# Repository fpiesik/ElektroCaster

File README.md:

What is the ElektroCaster?

The highest premise of the ElectroCaster is that it's a real guitar which can be used just like that. This project is about to extend the possibilities of expression of a guitar without taking anything away from it. By guitar I don't mean a specific instrument that's hacked somehow, but the idea of a guitar that's to be extended. The ElektroCaster is built from scratch out of aluminum, 3d printed PLA and wood. All the design files are made with open tools such as OpenScad and Kicad. The design is made with the option of parametric changes in mind, like changing the string count, for example.

Here is a list with the most important "guitar-extensions" I've implemented on the hardware side so far are:

    led lit fretboard with 150 individually controllable rbg-leds
    hexaphonic pickip along with a Teensy 4 based 6 channel dsp-unit
    actuator called Kickup that consists of 6 solenoid hitting the strings
    actuator called MultEbow that works like a polyphonic e-Bow (endless sustain)
    fretboard is "touch sensitive" in a way that it recognises which string was pressed at what position
    10 faders, 7 potis, 8 rotary encoder(&switches), 5 buttons, 7 toggle switches, 3 rotary switches (12steps), an analog joystick
    128*64 oled display

## Documentation quick reference

This repository contains three cooperating firmware targets. The tables below summarize the currently documented board roles, serial links, and hardware/protocol references without changing firmware behavior.

### Board roles

| Board firmware | Target noted in docs | Main role | Documentation |
| --- | --- | --- | --- |
| `software/firmwareHid` | Teensy 3.5 | Body controls, encoder/analog/digital input scanning, and local OLED rendering. | `docs/architecture.md`, `docs/protocols.md`, `docs/pinout.md` |
| `software/firmwareCtl` | Teensy 4.1 | Main controller for system state, LED fretboard, fretboard sensing, Kickup, MulEBow control, sequencer/MIDI/SD coordination, and board-to-board routing. | `docs/architecture.md`, `docs/protocols.md`, `docs/realtime.md` |
| `software/firmwareAudio` | Teensy 4.1 | Hexaphonic audio processing, pitch/amplitude analysis, per-string DSP, and actuator audio/control outputs. | `docs/architecture.md`, `docs/protocols.md`, `docs/realtime.md` |

### Serial protocol map

| Link | Baud | Purpose | Details |
| --- | ---: | --- | --- |
| HID <-> CTL | 115200 | Body-control events from HID to CTL and AsciiMassage display commands from CTL to HID. | `docs/protocols.md` |
| CTL <-> Audio | 250000 | Raw byte audio-control commands from CTL to Audio and pitch/amplitude status from Audio to CTL. | `docs/protocols.md` |

### Hardware and timing notes

| Topic | Documentation file | Notes |
| --- | --- | --- |
| Pin assignments | `docs/pinout.md` | Documents firmware-inferred pins only; hardware connector names remain open unless present in source. |
| Realtime intervals | `docs/realtime.md` | Documents LED, fretboard debounce, Kickup, display, clock, HID, and audio intervals. |
| Testing guidance | `docs/testing.md` | Lists safe checks and hardware validation areas. |

### User manual

The English, code-derived user manual is available at [`docs/user-manual.md`](docs/user-manual.md). It distinguishes implemented behavior from hardware details that cannot be confirmed from the repository.

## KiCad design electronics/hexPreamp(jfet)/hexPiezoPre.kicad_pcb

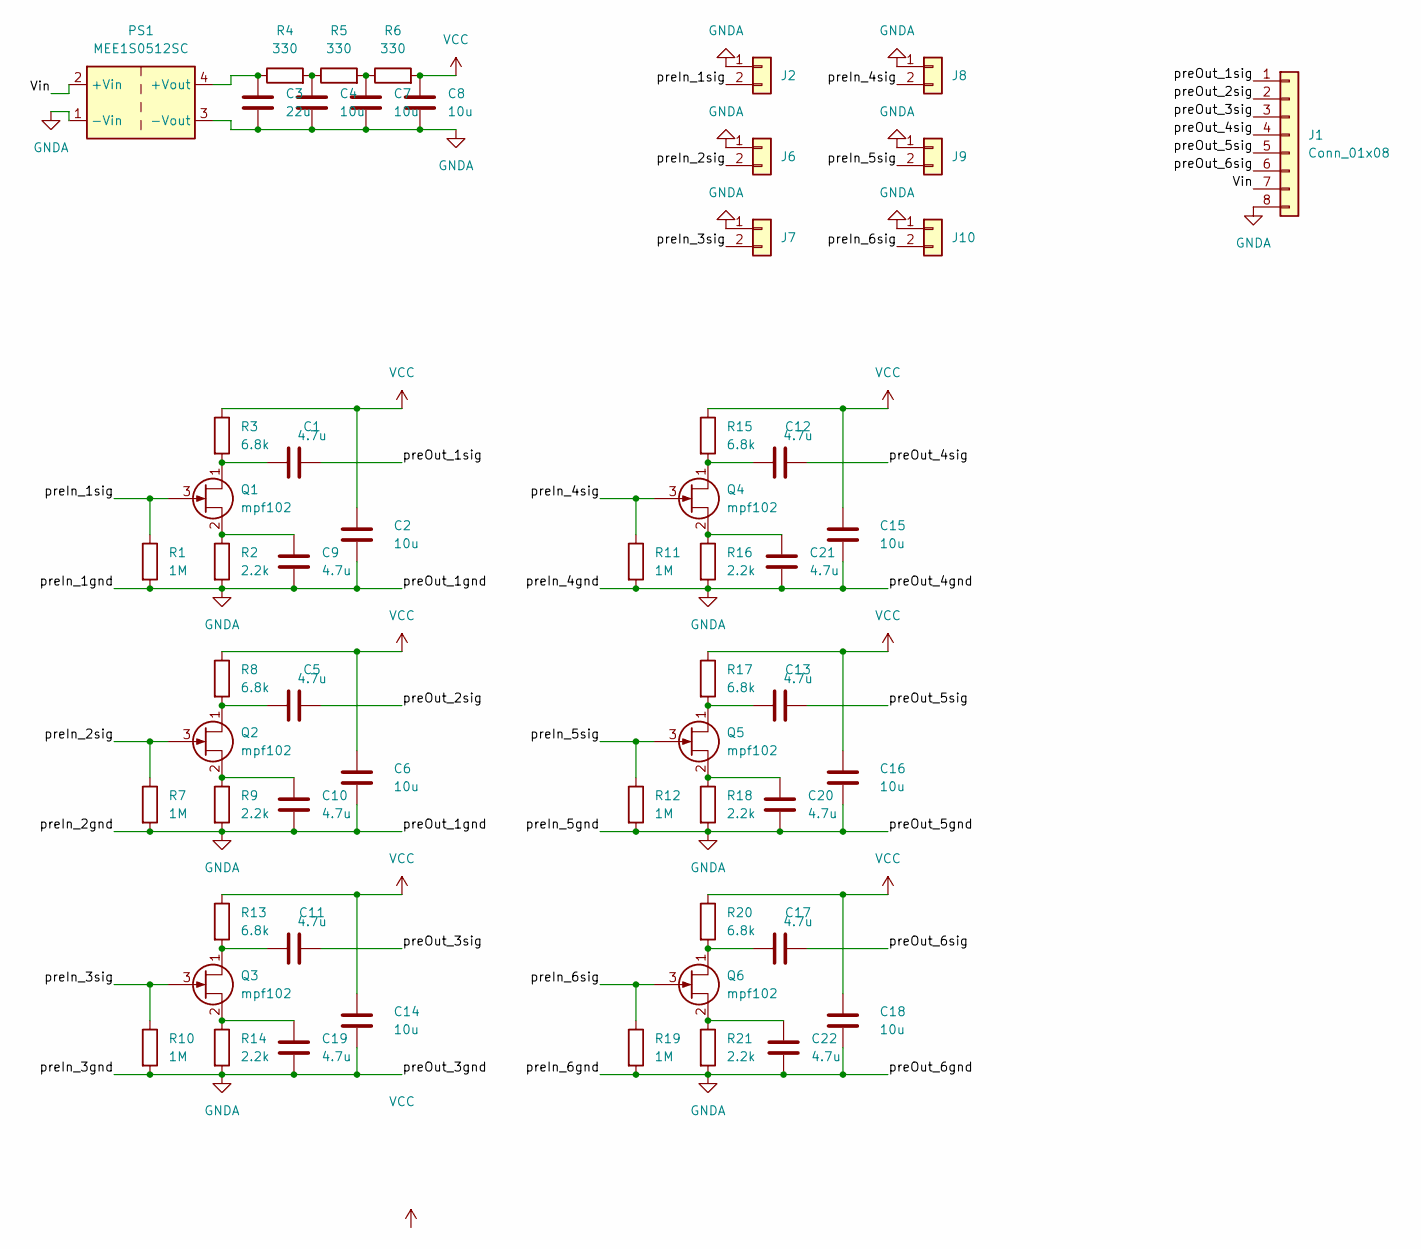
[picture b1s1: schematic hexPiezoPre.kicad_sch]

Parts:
C1, C5, C9, C10, C11, C12, C13, C17, C19, C20, C21, C22: 4.7u; C_0805_2012Metric_Pad1.18x1.45mm_HandSolder
C2, C4, C6, C7, C8, C14, C15, C16, C18: 10u; C_0805_2012Metric_Pad1.18x1.45mm_HandSolder
C3: 22u; C_0805_2012Metric_Pad1.18x1.45mm_HandSolder
J1: Conn_01x08; PinHeader_1x08_P2.54mm_Vertical
J2, J6, J7, J8, J9, J10: Conn_01x02; PinHeader_1x02_P2.54mm_Vertical
PS1: MEE1S0512SC; Converter_DCDC_Murata_MEE1SxxxxSC_THT
Q1, Q2, Q3, Q4, Q5, Q6: mpf102; TO-92
R1, R7, R10, R11, R12, R19: 1M; R_0805_2012Metric_Pad1.20x1.40mm_HandSolder
R2, R9, R14, R16, R18, R21: 2.2k; R_0805_2012Metric_Pad1.20x1.40mm_HandSolder
R3, R8, R13, R15, R17, R20: 6.8k; R_0805_2012Metric_Pad1.20x1.40mm_HandSolder
R4, R5, R6: 330; R_0805_2012Metric_Pad1.20x1.40mm_HandSolder

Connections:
/Vin: J1.7, PS1.2 (+Vin)
/preIn_1sig: J2.2, Q1.3 (G), R1.1
/preIn_2sig: J6.2, Q2.3 (G), R7.1
/preIn_3sig: J7.2, Q3.3 (G), R10.1
/preIn_4sig: J8.2, Q4.3 (G), R11.1
/preIn_5sig: J9.2, Q5.3 (G), R12.1
/preIn_6sig: J10.2, Q6.3 (G), R19.1
/preOut_1sig: C1.2, J1.1
/preOut_2sig: C5.2, J1.2
/preOut_3sig: C11.2, J1.3
/preOut_4sig: C12.2, J1.4
/preOut_5sig: C13.2, J1.5
/preOut_6sig: C17.2, J1.6
GNDA: C2.2, C3.2, C4.2, C6.2, C7.2, C8.2, C9.2, C10.2, C14.2, C15.2, C16.2, C18.2, C19.2, C20.2, C21.2, C22.2, J1.8, J2.1, J6.1, J7.1, J8.1, J9.1, J10.1, PS1.1 (-Vin), PS1.3 (-Vout), R1.2, R2.2, R7.2, R9.2, R10.2, R11.2, R12.2, R14.2, R16.2, R18.2, R19.2, R21.2
unnamed: C1.1, Q1.1 (D), R3.2
unnamed: C3.1, PS1.4 (+Vout), R4.1
unnamed: C4.1, R4.2, R5.1
unnamed: C5.1, Q2.1 (D), R8.2
unnamed: C7.1, R5.2, R6.1
unnamed: C9.1, Q1.2 (S), R2.1
unnamed: C10.1, Q2.2 (S), R9.1
unnamed: C11.1, Q3.1 (D), R13.2
unnamed: C12.1, Q4.1 (D), R15.2
unnamed: C13.1, Q5.1 (D), R17.2
unnamed: C17.1, Q6.1 (D), R20.2
unnamed: C19.1, Q3.2 (S), R14.1
unnamed: C20.1, Q5.2 (S), R18.1
unnamed: C21.1, Q4.2 (S), R16.1
unnamed: C22.1, Q6.2 (S), R21.1
VCC: C2.1, C6.1, C8.1, C14.1, C15.1, C16.1, C18.1, R3.1, R6.2, R8.1, R13.1, R15.1, R17.1, R20.1

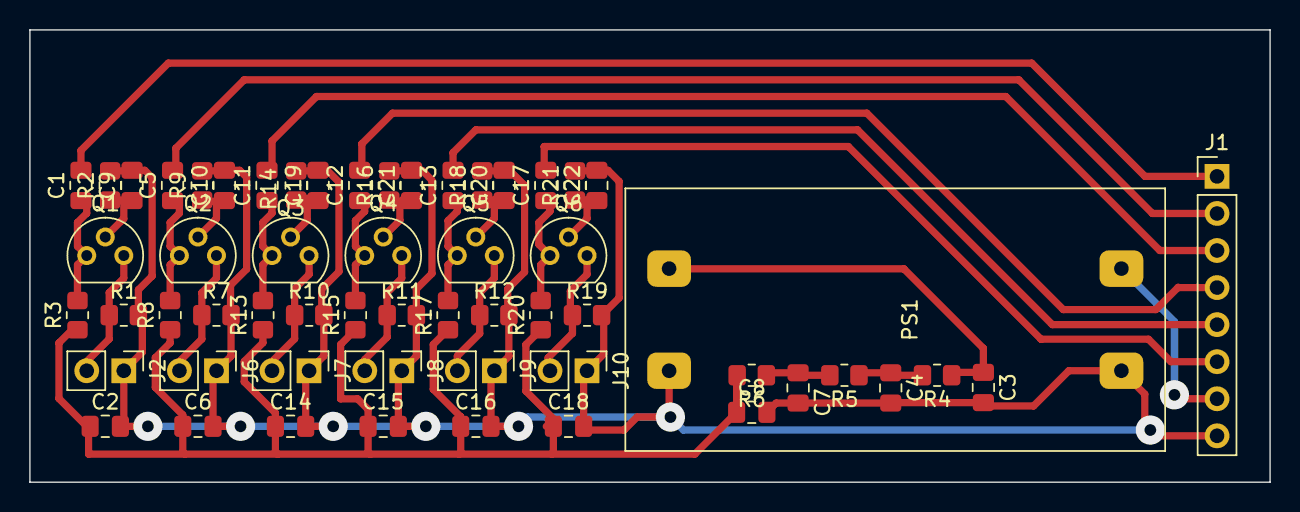
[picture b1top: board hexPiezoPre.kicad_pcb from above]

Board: 2 copper layers, 85.0 x 31.0 mm, 57 parts (0 on the bottom side), 30 nets.

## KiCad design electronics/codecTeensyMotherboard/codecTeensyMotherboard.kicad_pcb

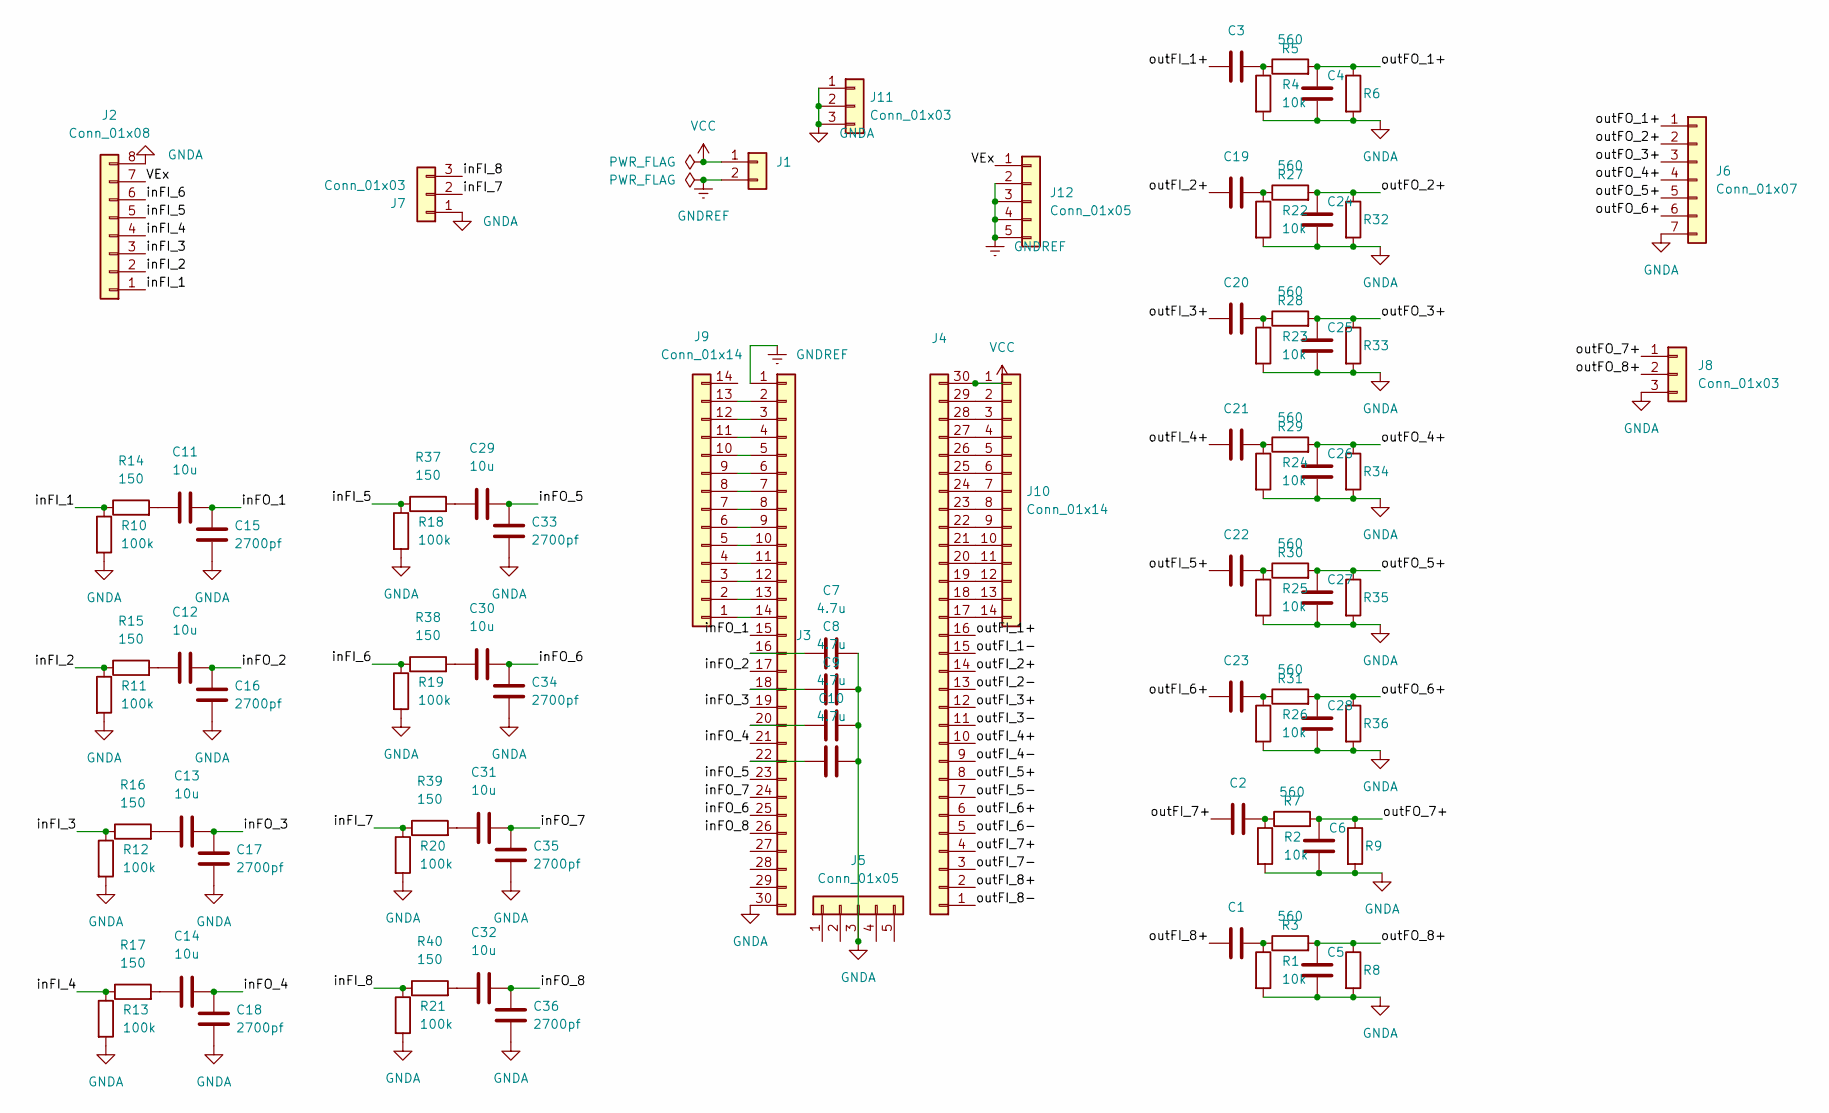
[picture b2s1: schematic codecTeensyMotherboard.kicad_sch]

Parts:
C1, C2, C3, C19, C20, C21, C22, C23: 3.3u; C_0805_2012Metric_Pad1.18x1.45mm_HandSolder
C4, C5, C6, C24, C25, C26, C27, C28: CAP; C_0805_2012Metric_Pad1.18x1.45mm_HandSolder
C7, C8, C9, C10: 4.7u; C_0805_2012Metric_Pad1.18x1.45mm_HandSolder
C11, C12, C13, C14, C29, C30, C31, C32: 10u; C_0805_2012Metric_Pad1.18x1.45mm_HandSolder
C15, C16, C17, C18, C33, C34, C35, C36: 2700pf; C_0805_2012Metric_Pad1.18x1.45mm_HandSolder
J1: Conn_01x02; PinHeader_1x02_P2.54mm_Vertical
J2: Conn_01x08; PinHeader_1x08_P2.54mm_Vertical
J3, J4: Conn_01x30; PinHeader_1x30_P2.54mm_Vertical
J5, J12: Conn_01x05; PinHeader_1x05_P2.54mm_Vertical
J6: Conn_01x07; PinHeader_1x07_P2.54mm_Vertical
J7, J8, J11: Conn_01x03; PinHeader_1x03_P2.54mm_Vertical
J9, J10: Conn_01x14; PinHeader_1x14_P2.54mm_Vertical
R1, R2, R4, R22, R23, R24, R25, R26: 10k; R_0805_2012Metric_Pad1.20x1.40mm_HandSolder
R3, R5, R7, R27, R28, R29, R30, R31: 560; R_0805_2012Metric_Pad1.20x1.40mm_HandSolder
R6, R8, R9, R32, R33, R34, R35, R36: R; R_0805_2012Metric_Pad1.20x1.40mm_HandSolder
R10, R11, R12, R13, R18, R19, R20, R21: 100k; R_0805_2012Metric_Pad1.20x1.40mm_HandSolder
R14, R15, R16, R17, R37, R38, R39, R40: 150; R_0805_2012Metric_Pad1.20x1.40mm_HandSolder

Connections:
/VEx: J2.7, J12.1
/inFI_1: J2.1, R10.1, R14.1
/inFI_2: J2.2, R11.1, R15.1
/inFI_3: J2.3, R12.1, R16.1
/inFI_4: J2.4, R13.1, R17.1
/inFI_5: J2.5, R18.1, R37.1
/inFI_6: J2.6, R19.1, R38.1
/inFI_7: J7.2, R20.1, R39.1
/inFI_8: J7.3, R21.1, R40.1
/inFO_1: C11.2, C15.2, J3.15
/inFO_2: C12.2, C16.2, J3.17
/inFO_3: C13.2, C17.2, J3.19
/inFO_4: C14.2, C18.2, J3.21
/inFO_5: C29.2, C33.2, J3.23
/inFO_6: C30.2, C34.2, J3.25
/inFO_7: C31.2, C35.2, J3.24
/inFO_8: C32.2, C36.2, J3.26
/outFI_1+: C3.1, J4.16
/outFI_1-: J4.15
/outFI_2+: C19.1, J4.14
/outFI_2-: J4.13
/outFI_3+: C20.1, J4.12
/outFI_3-: J4.11
/outFI_4+: C21.1, J4.10
/outFI_4-: J4.9
/outFI_5+: C22.1, J4.8
/outFI_5-: J4.7
/outFI_6+: C23.1, J4.6
/outFI_6-: J4.5
/outFI_7+: C2.1, J4.4
/outFI_7-: J4.3
/outFI_8+: C1.1, J4.2
/outFI_8-: J4.1
/outFO_1+: C4.1, J6.1, R5.2, R6.1
/outFO_2+: C24.1, J6.2, R27.2, R32.1
/outFO_3+: C25.1, J6.3, R28.2, R33.1
/outFO_4+: C26.1, J6.4, R29.2, R34.1
/outFO_5+: C27.1, J6.5, R30.2, R35.1
/outFO_6+: C28.1, J6.6, R31.2, R36.1
/outFO_7+: C6.1, J8.1, R7.2, R9.1
/outFO_8+: C5.1, J8.2, R3.2, R8.1
GNDA: C4.2, C5.2, C6.2, C7.2, C8.2, C9.2, C10.2, C15.1, C16.1, C17.1, C18.1, C24.2, C25.2, C26.2, C27.2, C28.2, C33.1, C34.1, C35.1, C36.1, J2.8, J3.30, J5.3, J6.7, J7.1, J8.3, J11.1, J11.2, J11.3, R1.2, R2.2, R4.2, R6.2, R8.2, R9.2, R10.2, R11.2, R12.2, R13.2, R18.2, R19.2, R20.2, R21.2, R22.2, R23.2, R24.2, R25.2, R26.2, R32.2, R33.2, R34.2, R35.2, R36.2
GNDREF: J1.2, J3.1, J12.2, J12.3, J12.4, J12.5
unnamed: C1.2, R1.1, R3.1
unnamed: C2.2, R2.1, R7.1
unnamed: C3.2, R4.1, R5.1
unnamed: C7.1, J3.16
unnamed: C8.1, J3.18
unnamed: C9.1, J3.20
unnamed: C10.1, J3.22
unnamed: C11.1, R14.2
unnamed: C12.1, R15.2
unnamed: C13.1, R16.2
unnamed: C14.1, R17.2
unnamed: C19.2, R22.1, R27.1
unnamed: C20.2, R23.1, R28.1
unnamed: C21.2, R24.1, R29.1
unnamed: C22.2, R25.1, R30.1
unnamed: C23.2, R26.1, R31.1
unnamed: C29.1, R37.2
unnamed: C30.1, R38.2
unnamed: C31.1, R39.2
unnamed: C32.1, R40.2
unnamed: J3.2, J9.13
unnamed: J3.3, J9.12
unnamed: J3.4, J9.11
unnamed: J3.5, J9.10
unnamed: J3.6, J9.9
unnamed: J3.7, J9.8
unnamed: J3.8, J9.7
unnamed: J3.9, J9.6
unnamed: J3.10, J9.5
unnamed: J3.11, J9.4
unnamed: J3.12, J9.3
unnamed: J3.13, J9.2
unnamed: J3.14, J9.1
unnamed: J4.29, J10.2
unnamed: J4.28, J10.3
unnamed: J4.27, J10.4
unnamed: J4.26, J10.5
unnamed: J4.25, J10.6
unnamed: J4.24, J10.7
unnamed: J4.23, J10.8
unnamed: J4.22, J10.9
unnamed: J4.21, J10.10
unnamed: J4.20, J10.11
unnamed: J4.19, J10.12
unnamed: J4.18, J10.13
unnamed: J4.17, J10.14
VCC: J1.1, J4.30, J10.1

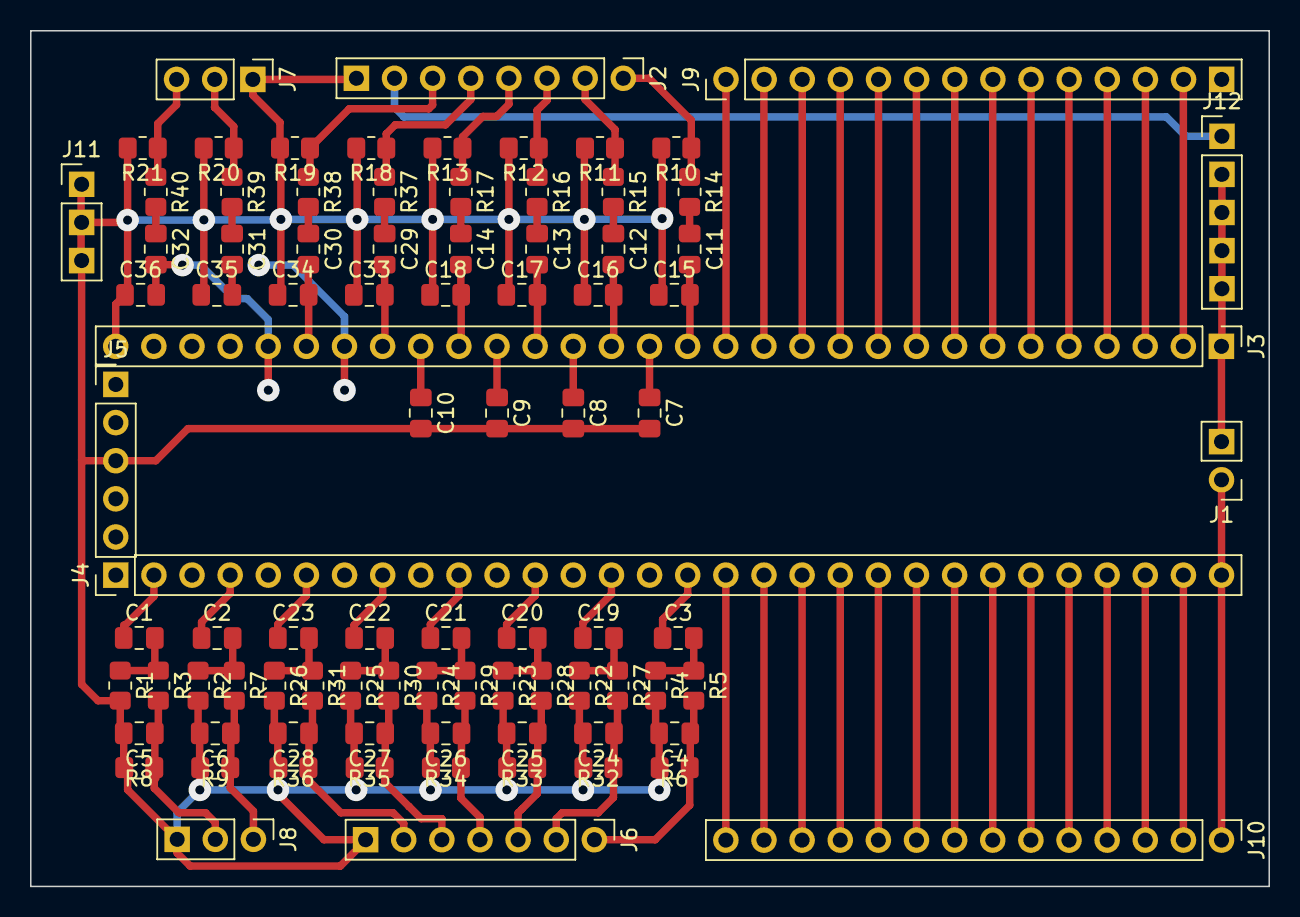
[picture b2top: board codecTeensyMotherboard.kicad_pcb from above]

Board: 2 copper layers, 82.5 x 57.0 mm, 88 parts (0 on the bottom side), 82 nets.

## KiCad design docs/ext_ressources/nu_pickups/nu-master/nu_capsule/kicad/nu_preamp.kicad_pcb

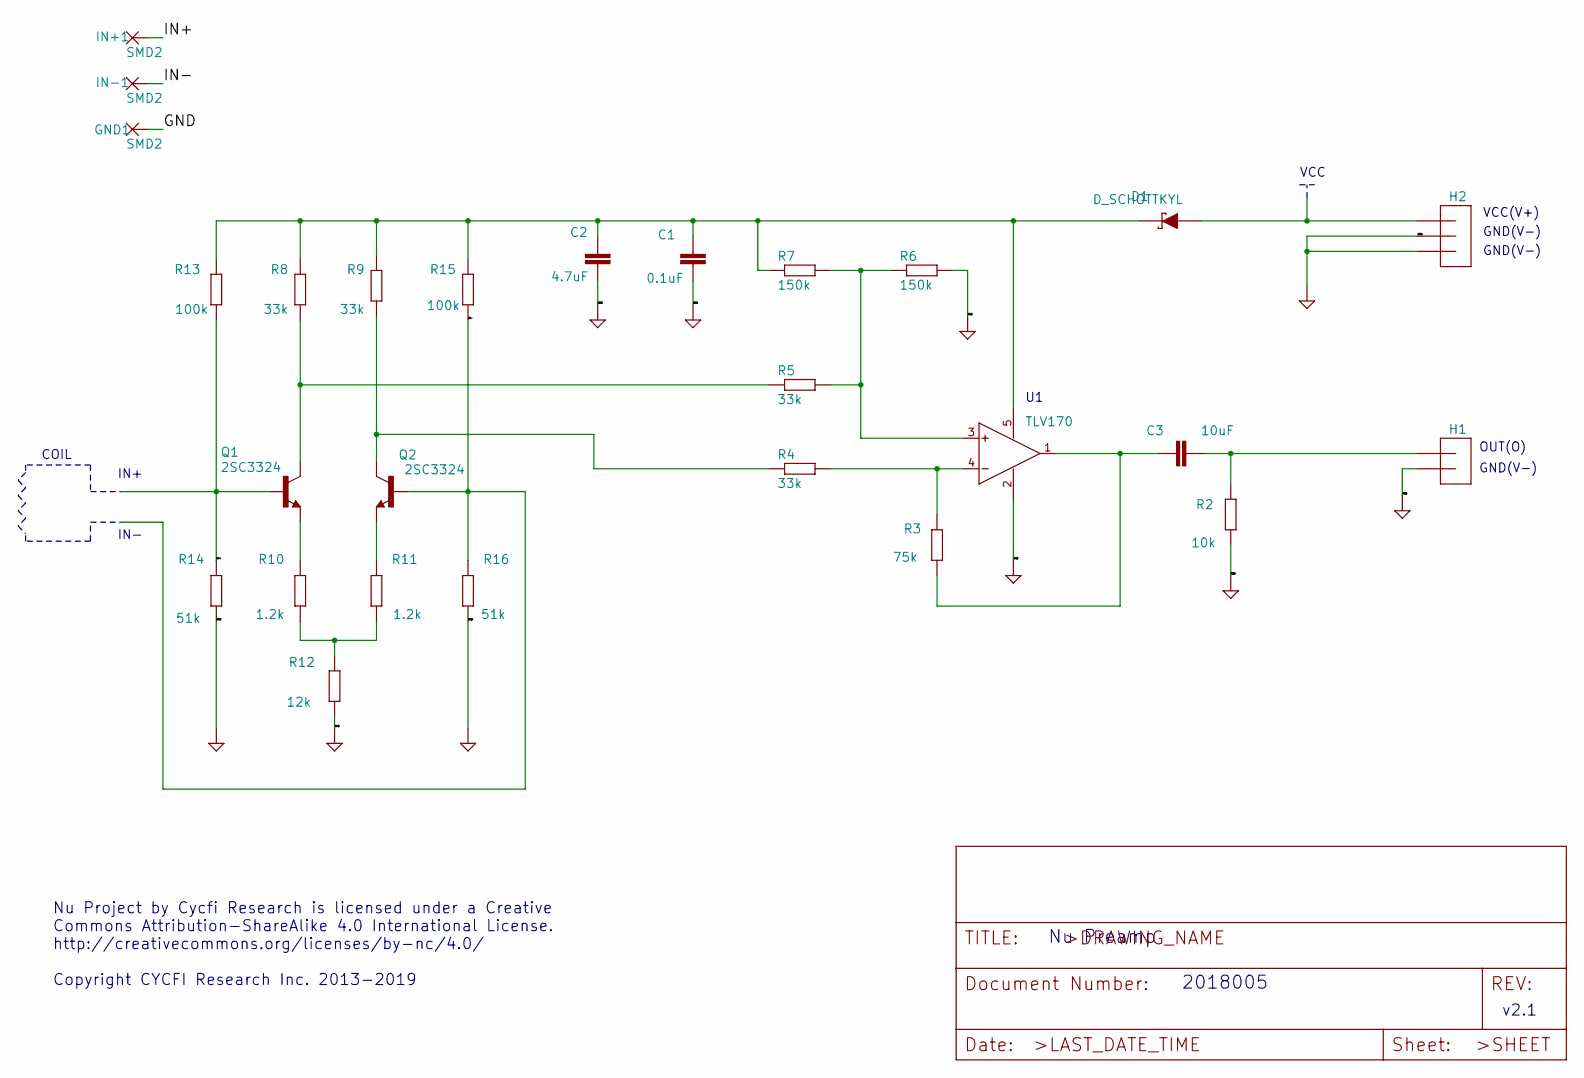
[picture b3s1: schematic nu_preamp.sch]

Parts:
C1: 0.1uF; C0402
C2: 4.7uF; C0603_NK
C3: 10uF; C0603_NK
D1: D_SCHOTTKYL; SOD-323
GND1: SMD2; SMD1,27-2,54
H1: 2P-2MM-TH-MALE; 2P-2MM-TH
H2: 3P-2MM-TH-MALE; 3P-2MM-TH
IN+1: SMD2; SMD1,27-2,54
IN-1: SMD2; SMD1,27-2,54
Q1, Q2: 2SC3324; SOT23
R2: 10k; R0402
R3: 75k; R0402
R4, R5, R8, R9: 33k; R0402
R6, R7: 150k; R0402
R10, R11: 1.2k; R0402
R12: 12k; R0402
R13, R15: 100k; R0402
R14, R16: 51k; R0402
U1: TLV170; SOT23-5

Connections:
/IN+: IN+1.1, Q1.1 (B), R13.1, R14.2
/IN-: IN-1.1, Q2.1 (B), R15.1, R16.2
GND: C1.2, C2.1, GND1.1, H1.P$2 (2), H2.P$2 (2), H2.P$3 (3), R2.1, R6.2, R12.1, R14.1, R16.1, U1.2 (V-)
unnamed: C1.1, C2.2, D1.2 (C), R7.1, R8.2, R9.2, R13.2, R15.2, U1.5 (V+)
unnamed: C3.1, R3.1, U1.1 (OUT)
unnamed: C3.2, H1.P$1 (1), R2.2
unnamed: D1.1 (A), H2.P$1 (1)
unnamed: Q1.2 (E), R10.2
unnamed: Q1.3 (C), R5.1, R8.1
unnamed: Q2.2 (E), R11.2
unnamed: Q2.3 (C), R4.1, R9.1
unnamed: R3.2, R4.2, U1.4 (IN-)
unnamed: R5.2, R6.1, R7.2, U1.3 (IN+)
unnamed: R10.1, R11.1, R12.2

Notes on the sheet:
Nu Preamp
v2.1
Nu Project by Cycfi Research is licensed under a Creative Commons Attribution-ShareAlike 4.0 International License. http://creativecommons.org/licenses/by-nc/4.0/ Copyright CYCFI Research Inc. 2013-2019
VCC
COIL
VCC(V+)
GND(V-)
OUT(O)
IN+
IN-
2018005

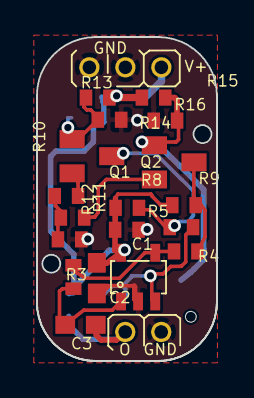
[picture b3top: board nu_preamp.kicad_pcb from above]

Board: 2 copper layers, 10.0 x 18.0 mm, 28 parts (0 on the bottom side), 14 nets.

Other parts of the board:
@HOLE0: (no value)

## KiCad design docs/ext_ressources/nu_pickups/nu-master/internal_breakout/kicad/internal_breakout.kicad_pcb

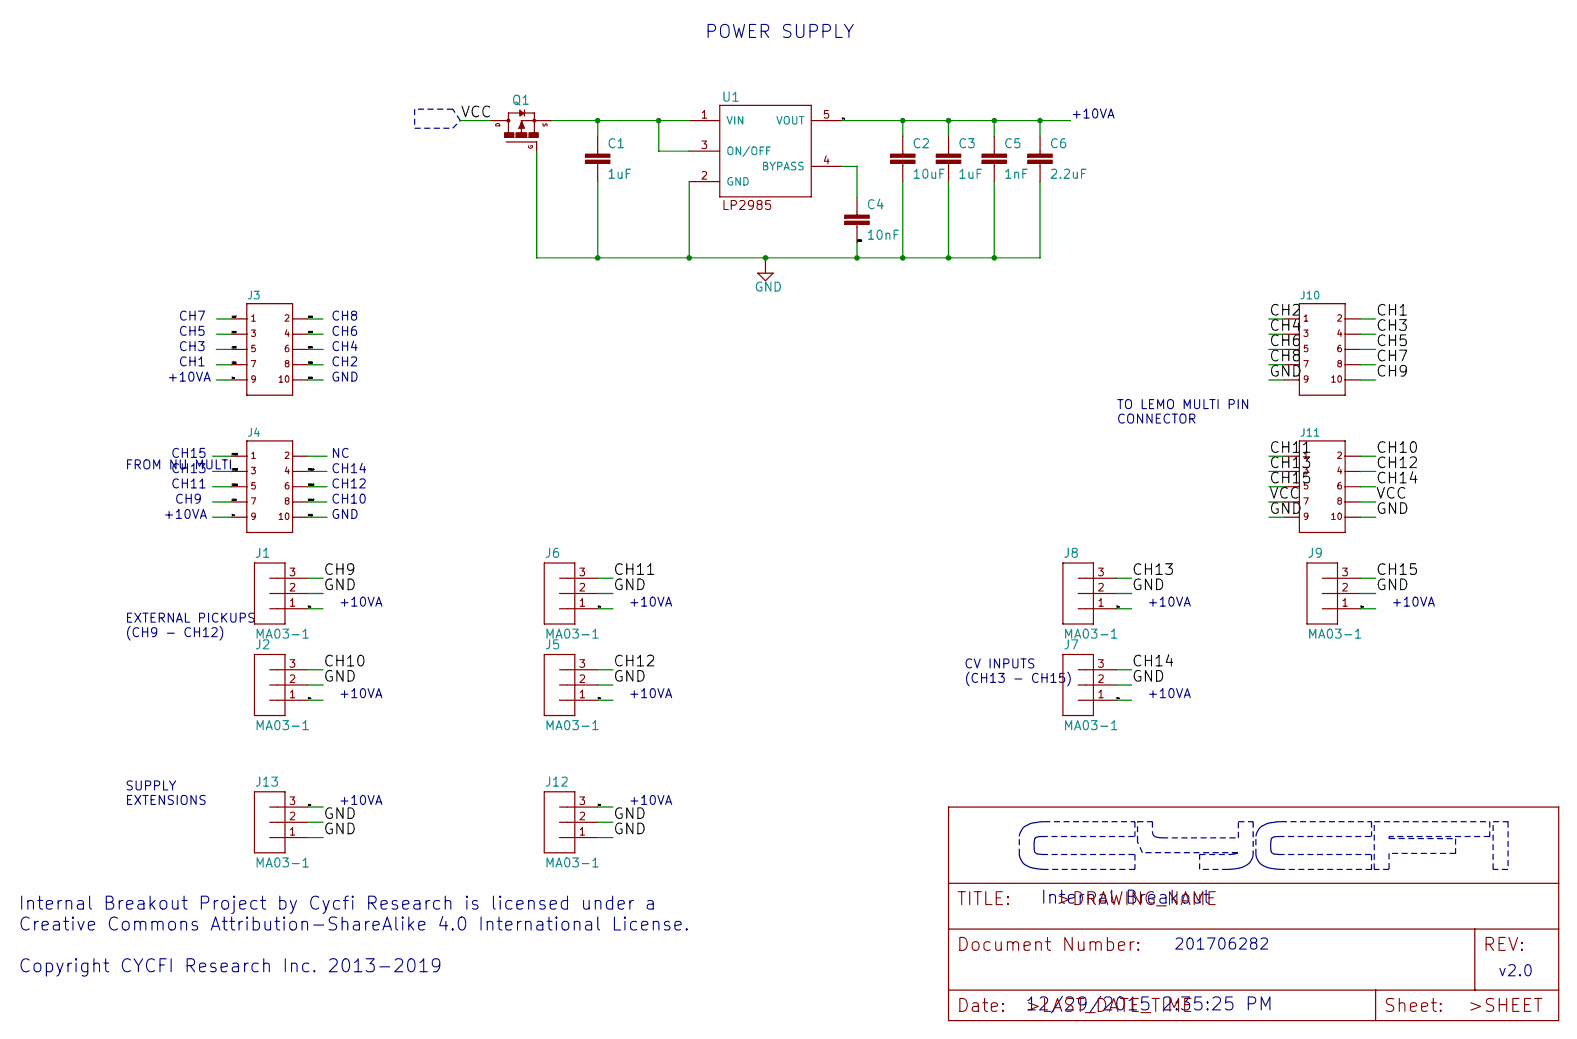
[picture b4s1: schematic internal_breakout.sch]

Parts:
C1, C3: 1uF; C0603
C2: 10uF; C0603
C4: 10nF; C0402
C5: 1nF; C0402
C6: 2.2uF; C0603
J1, J2, J5, J6, J7, J8, J9, J12, J13: MA03-1
J3, J4, J10, J11: 2X5
Q1: DMP3099L; SUPER-SOT3
U1: LP2985; SOT25

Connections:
/CH1: J3.7, J10.2
/CH2: J3.8, J10.1
/CH3: J3.5, J10.4
/CH4: J3.6, J10.3
/CH5: J3.3, J10.6
/CH6: J3.4, J10.5
/CH7: J3.1, J10.8
/CH8: J3.2, J10.7
/CH9: J1.3, J4.7, J10.10
/CH10: J2.3, J4.8, J11.2
/CH11: J4.5, J6.3, J11.1
/CH12: J4.6, J5.3, J11.4
/CH13: J4.3, J8.3, J11.3
/CH14: J4.4, J7.3, J11.6
/CH15: J4.1, J9.3, J11.5
/V+: C2.1, C3.1, C5.1, C6.1, J1.1, J2.1, J3.9, J4.9, J5.1, J6.1, J7.1, J8.1, J9.1, J12.3, J13.3, U1.5 (VOUT)
/VCC: J11.7, J11.8, Q1.3 (D)
GND: C1.2, C2.2, C3.2, C4.2, C5.2, C6.2, J1.2, J2.2, J3.10, J4.10, J5.2, J6.2, J7.2, J8.2, J9.2, J10.9, J11.9, J11.10, J12.1, J12.2, J13.1, J13.2, Q1.1 (G), U1.2 (GND)
unnamed: C1.1, Q1.2 (S), U1.1 (VIN), U1.3 (ON/OFF)
unnamed: C4.1, U1.4 (BYPASS)

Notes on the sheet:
POWER SUPPLY
Internal Breakout
v2.0
Internal Breakout Project by Cycfi Research is licensed under a Creative Commons Attribution-ShareAlike 4.0 International License. Copyright CYCFI Research Inc. 2013-2019
201706282
12/29/2015 2:35:25 PM
+10VA
CH1
CH3
CH5
CH7
GND
CH2
CH4
CH6
CH8
FROM NU MULTI
EXTERNAL PICKUPS (CH9 - CH12)
SUPPLY EXTENSIONS
CV INPUTS (CH13 - CH15)
TO LEMO MULTI PIN CONNECTOR
CH9
CH10
CH11
CH12
CH13
CH14
CH15

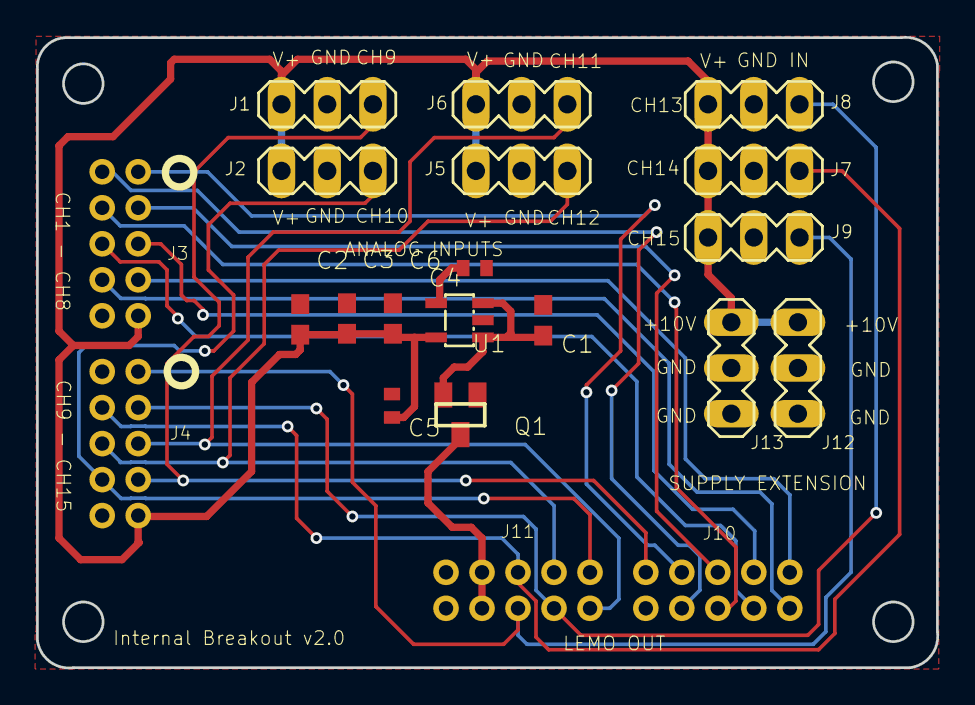
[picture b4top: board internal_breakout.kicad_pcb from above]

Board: 2 copper layers, 50.0 x 35.0 mm, 21 parts (0 on the bottom side), 20 nets.

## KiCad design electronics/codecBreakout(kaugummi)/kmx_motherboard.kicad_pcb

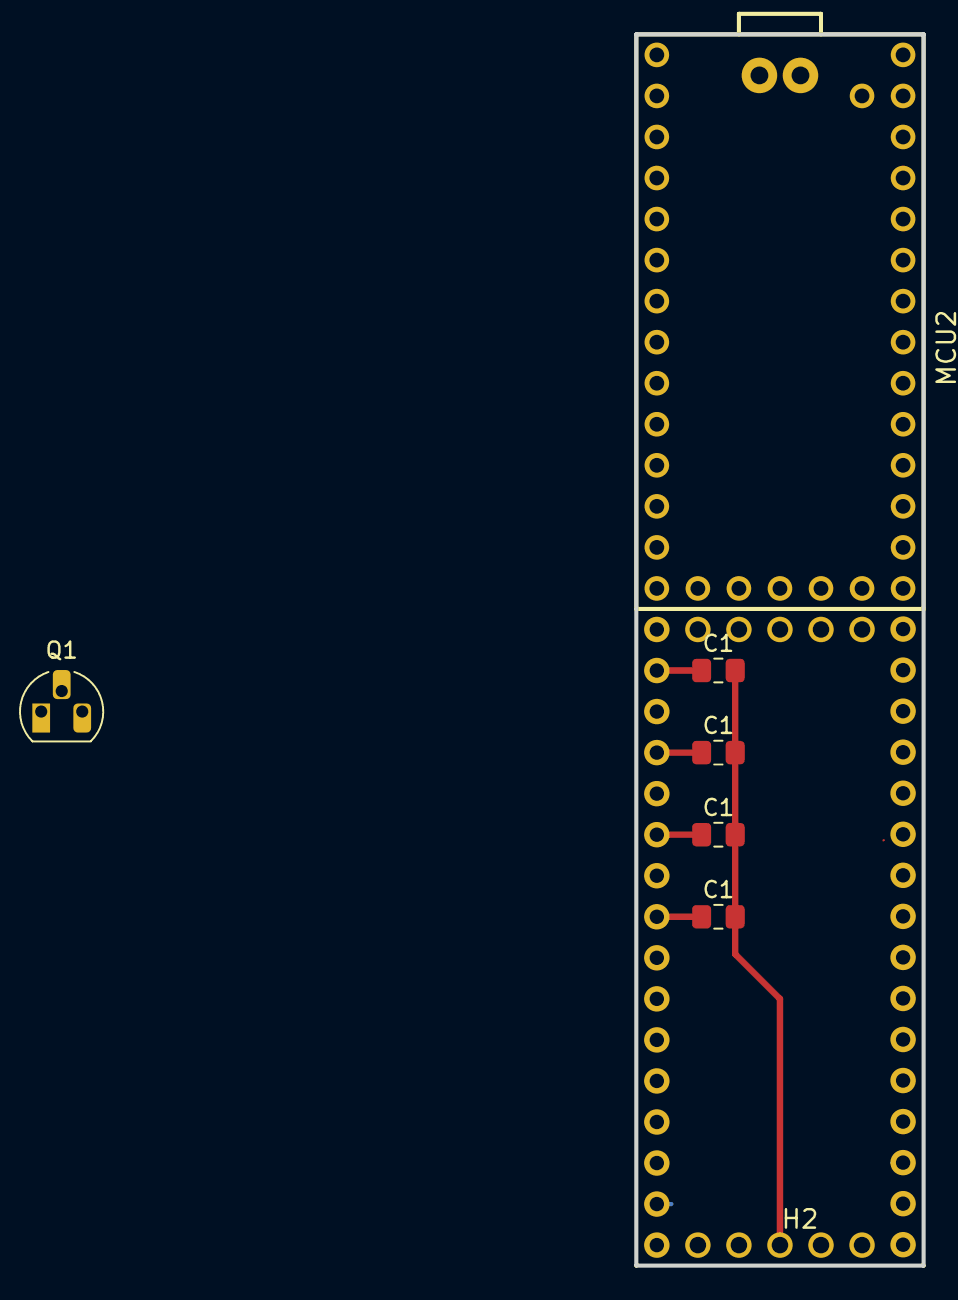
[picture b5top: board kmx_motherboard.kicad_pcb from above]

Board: 2 copper layers, 17.8 x 76.2 mm, 10 parts (0 on the bottom side), 7 nets.

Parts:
C1, C1#2, C1#3, C1#4: 4.7u; C_0805_2012Metric_Pad1.18x1.45mm_HandSolder
H1, H2: Header-2.54_1x5; HDR-5X1_2.54
MCU2: TEENSY 4.0 W. USB ONLY
P1, P2: Header-2.54_1x16; HDR-16X1_2.54
Q1: MPF102; TO-92L_HandSolder

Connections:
+5V: H2.4, P1.15
GND: MCU2.GND0, MCU2.GND1, MCU2.GND2, P1.16
LRCK: H1.3, MCU2.20
MCLK: H1.1, MCU2.23
SCLK: H1.2, MCU2.21
SDIN: H1.4, MCU2.7
SDOUT: H1.5, MCU2.8

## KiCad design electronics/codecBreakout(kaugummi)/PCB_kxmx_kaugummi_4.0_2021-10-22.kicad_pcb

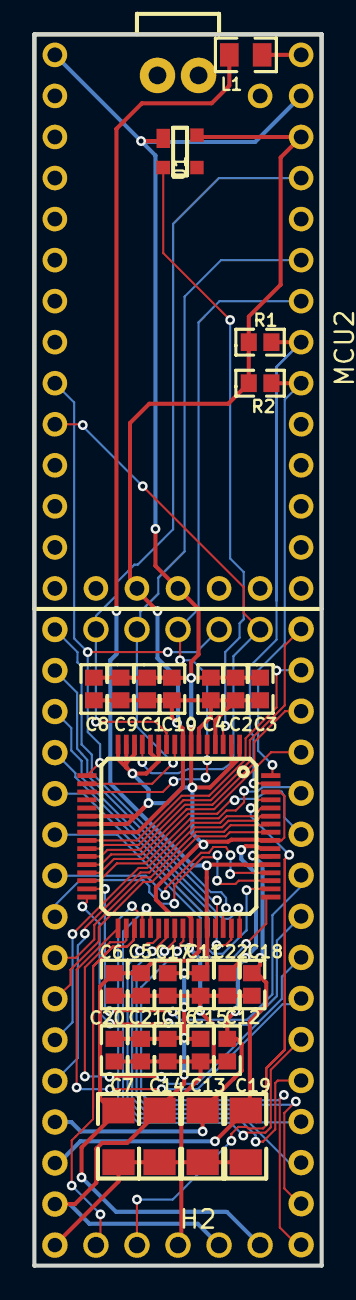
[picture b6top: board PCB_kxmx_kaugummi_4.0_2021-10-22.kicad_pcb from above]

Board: 2 copper layers, 17.8 x 76.2 mm, 32 parts (0 on the bottom side), 45 nets.

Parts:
C1, C2, C3, C5, C9, C11, C16, C18, C21: 100nF; 0603
C4, C10, C17, C22: 100pF; 0603
C6, C8, C15, C20: 10uF; 0603
C7, C13, C14, C19: 100uF; 1206
C12: 22uF; 0603
H1, H2: Header-2.54_1x5; HDR-5X1/2.54
L1: 220Ω; 0805
MCU2: TEENSY 4.0 W. USB ONLY
P1, P2: Header-2.54_1x16; HDR-16X1/2.54
R1, R2: 2K; 0603
U1: CAT811TTBI-GT3; SOT-143
U2: CS42448; LQFP64-10X10

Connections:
+3V3: C1.2, C2.2, C3.2, C4.1, C8.2, C9.2, C10.1, MCU2.3, R1.1, R2.1, U1.4, U2.4, U2.6, U2.8, U2.24
+5V: C14.2, C15.2, C16.2, C17.1, C20.2, C21.2, C22.1, H2.4, L1.2, P1.15, U2.44, U2.53
FILT+_ADC: C11.2, C12.1, C13.2, P1.13, U2.55
FILT+_DAC: C18.2, C19.2, P1.14, U2.54
GND: C1.1, C2.1, C3.1, C4.2, C5.1, C6.1, C7.1, C8.1, C9.1, C10.2, C11.1, C12.2, C13.1, C14.1, C15.1, C16.1, C17.2, C18.1, C19.1, C20.1, C21.1, C22.2, H2.3, MCU2.GND0, MCU2.GND1, MCU2.GND2, P1.16, U1.1, U2.1, U2.2, U2.7, U2.11, U2.12, U2.14, U2.15, U2.16, U2.22, U2.23, U2.42, U2.56, U2.62
IN1+: P1.1, U2.46
IN1-: P1.2, U2.45
IN2+: P1.3, U2.48
IN2-: P1.4, U2.47
IN3+: P1.5, U2.50
IN3-: P1.6, U2.49
IN4+: P1.7, U2.52
IN4-: P1.8, U2.51
IN5+: P1.9, U2.58
IN5-: P1.10, U2.57
IN6+: P1.11, U2.60
IN6-: P1.12, U2.59
INT: H2.2, U2.61
L1_1: L1.1, MCU2.VIN
LRCK: H1.3, MCU2.20, U2.5, U2.19
MCLK: H1.1, MCU2.23, U2.10
MUTEC: H2.1, U2.35
OUT1+: P2.1, U2.26
OUT1-: P2.2, U2.25
OUT2+: P2.3, U2.27
OUT2-: P2.4, U2.28
OUT3+: P2.5, U2.30
OUT3-: P2.6, U2.29
OUT4+: P2.7, U2.31
OUT4-: P2.8, U2.32
OUT5+: P2.9, U2.34
OUT5-: P2.10, U2.33
OUT6+: P2.11, U2.36
OUT6-: P2.12, U2.37
OUT7+: P2.13, U2.39
OUT7-: P2.14, U2.38
OUT8+: P2.15, U2.40
OUT8-: P2.16, U2.41
RST: U1.2, U2.3
SCL: MCU2.19, R1.2, U2.63
SCLK: H1.2, MCU2.21, U2.9, U2.18
SDA: MCU2.18, R2.2, U2.64
SDIN: H1.4, MCU2.7, U2.17
SDOUT: H1.5, MCU2.8, U2.13
VQ: C5.2, C6.2, C7.2, H2.5, U2.43

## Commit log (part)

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2019-02-02 init-allSoFar
2019-02-03 added string mute function to sequencer
2019-05-20 added breakout-box-case, some firmwarechanges
2019-05-20 added docs folder with initial bom
2020-10-20 New neck-design with parametric led-pcb
2020-10-20 added other electronic-files
2021-02-15 added polytuner, made notefreq work with different buffer size
2022-02-02 new preamp, switched to teensy 4.0
2022-05-02 new sequencer
2022-05-03 pattern switch bug workaround
    workaround by scanning through all patterns at startup
2022-05-08 added adapter for power over usb-c
2022-06-13 genSq update and external midi instrument function
2022-06-27 genSq: control channel
2023-06-19 sync after while
2023-12-02 to much to tell
2025-10-17 different changes
2025-12-13 multibow: delays to compensate latency
2026-06-17 clean unused
2026-06-17 docs: add refactor safety foundation
2026-06-18 Name serial protocol command codes
